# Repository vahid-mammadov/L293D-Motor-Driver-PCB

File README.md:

# L293D Motor Driver PCB

## Overview
A custom motor driver PCB designed for controlling DC motors using the **L293D H-Bridge motor driver**. 
The board was designed as part of an embedded systems and electronics development project.

## Features
Dual DC motor control using L293D
H-Bridge motor driver configuration
74HC595 shift register for digital output expansion
External power and motor connection interfaces
Custom schematic and PCB layout

## Tools & Technologies
**KiCad**
PCB Design
Electronic Circuit Design
L293D H-Bridge Motor Driver
74HC595 Shift Register

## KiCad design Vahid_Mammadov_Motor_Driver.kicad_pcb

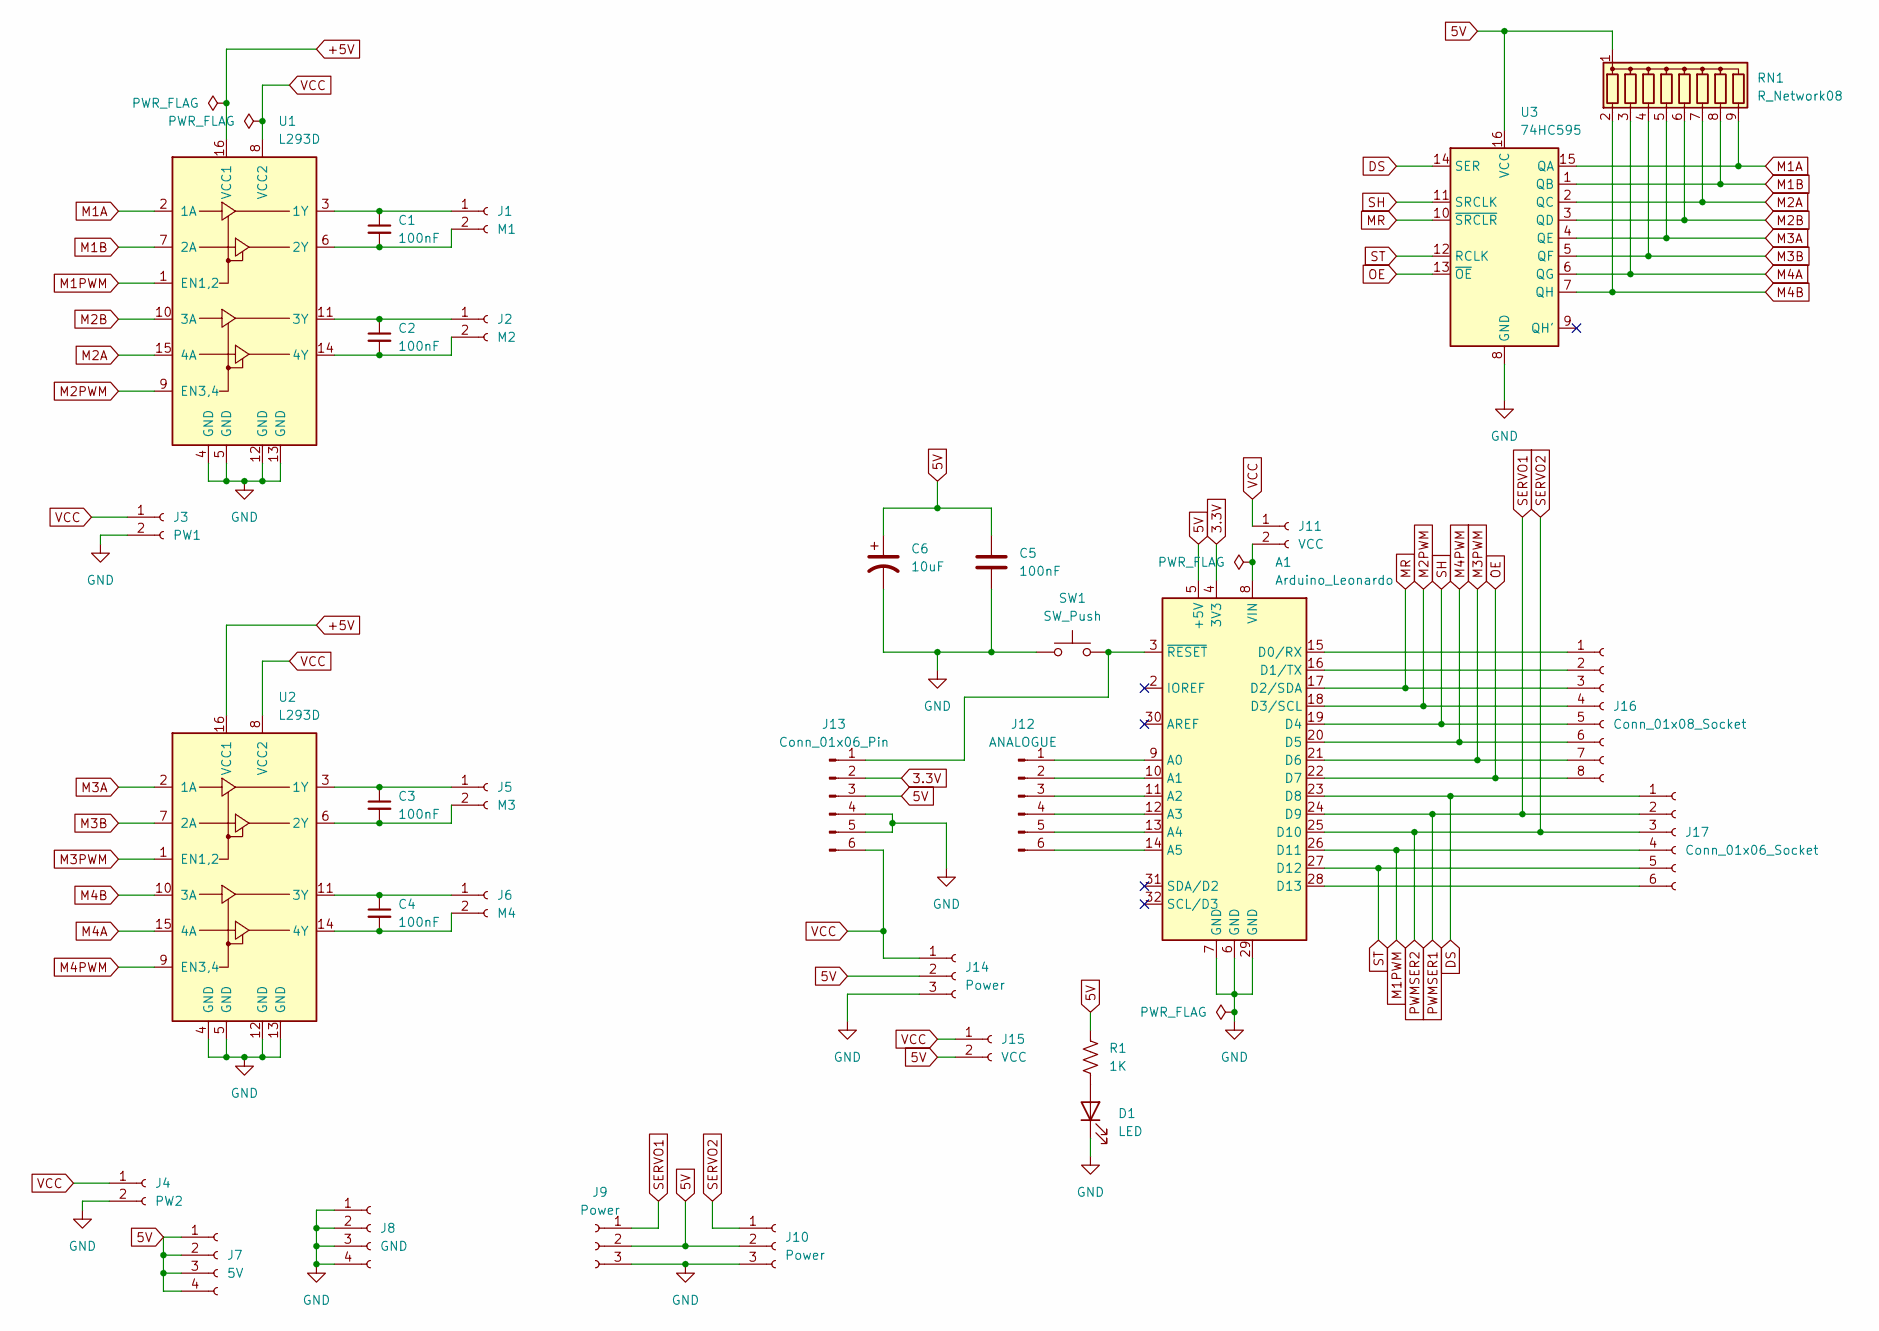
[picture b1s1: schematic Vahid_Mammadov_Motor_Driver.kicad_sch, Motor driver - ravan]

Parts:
A1: Arduino_Leonardo; Arduino_UNO_R3
C1, C2, C3, C4, C5: 100nF; CP_Radial_D4.0mm_P1.50mm
C6: 10uF; CP_Radial_D5.0mm_P2.50mm
D1: LED; LED_2010_5025Metric_Pad1.52x2.65mm_HandSolder
J1: M1; PinHeader_1x02_P2.00mm_Vertical
J2: M2; PinHeader_1x02_P2.00mm_Vertical
J3: PW1; PinHeader_1x02_P2.00mm_Vertical
J4: PW2; PinHeader_1x02_P2.00mm_Vertical
J5: M3; PinHeader_1x02_P2.00mm_Vertical
J6: M4; PinHeader_1x02_P2.00mm_Vertical
J7: 5V; PinHeader_1x04_P2.00mm_Vertical
J8: GND; PinHeader_1x04_P2.00mm_Vertical
J9, J10, J14: Power; PinHeader_1x03_P2.00mm_Vertical
J11, J15: VCC; PinHeader_1x02_P2.00mm_Vertical
J12: ANALOGUE; PinHeader_1x06_P2.00mm_Vertical
J13: Conn_01x06_Pin; PinHeader_1x06_P2.00mm_Vertical
J16: Conn_01x08_Socket; PinHeader_1x08_P2.00mm_Vertical
J17: Conn_01x06_Socket; PinHeader_1x08_P2.00mm_Vertical
R1: 1K; R_Axial_DIN0204_L3.6mm_D1.6mm_P5.08mm_Horizontal
RN1: R_Network08; R_Array_SIP9
SW1: SW_Push; SW_PUSH_6mm
U1, U2: L293D; DIP-16_W7.62mm
U3: 74HC595; DIP-16_W7.62mm

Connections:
3.3V: A1.4 (3V3), J13.2
5V: A1.5 (+5V), C5.1, C6.1, J7.1, J7.2, J7.3, J7.4, J9.2, J10.2, J13.3, J14.2, J15.2, R1.1, RN1.1 (common), U3.16 (VCC)
+5V: U1.16 (VCC1), U2.16 (VCC1)
DS: A1.23 (D8), J17.1, U3.14 (SER)
GND: A1.6 (GND), A1.7 (GND), A1.29 (GND), C5.2, C6.2, D1.1 (K), J3.2, J4.2, J8.1, J8.2, J8.3, J8.4, J9.3, J10.3, J13.4, J13.5, J14.3, SW1.1, U1.4 (GND), U1.5 (GND), U1.12 (GND), U1.13 (GND), U2.4 (GND), U2.5 (GND), U2.12 (GND), U2.13 (GND), U3.8 (GND)
M1A: RN1.9 (R8), U1.2 (1A), U3.15 (QA)
M1B: RN1.8 (R7), U1.7 (2A), U3.1 (QB)
M1PWM: A1.26 (D11), J17.4, U1.1 (EN1,2)
M2A: RN1.7 (R6), U1.15 (4A), U3.2 (QC)
M2B: RN1.6 (R5), U1.10 (3A), U3.3 (QD)
M2PWM: A1.18 (D3/SCL), J16.4, U1.9 (EN3,4)
M3A: RN1.5 (R4), U2.2 (1A), U3.4 (QE)
M3B: RN1.4 (R3), U2.7 (2A), U3.5 (QF)
M3PWM: A1.21 (D6), J16.7, U2.1 (EN1,2)
M4A: RN1.3 (R2), U2.15 (4A), U3.6 (QG)
M4B: RN1.2 (R1), U2.10 (3A), U3.7 (QH)
M4PWM: A1.20 (D5), J16.6, U2.9 (EN3,4)
MR: A1.17 (D2/SDA), J16.3, U3.10 (~SRCLR)
unnamed: A1.9 (A0), J12.1
unnamed: A1.10 (A1), J12.2
unnamed: A1.11 (A2), J12.3
unnamed: A1.12 (A3), J12.4
unnamed: A1.13 (A4), J12.5
unnamed: A1.14 (A5), J12.6
unnamed: A1.15 (D0/RX), J16.1
unnamed: A1.16 (D1/TX), J16.2
unnamed: A1.28 (D13), J17.6
unnamed: A1.8 (VIN), J11.2
unnamed: A1.3 (~RESET), J13.1, SW1.2
unnamed: D1.2 (A), R1.2
unnamed: C1.1, J1.1, U1.3 (1Y)
unnamed: C1.2, J1.2, U1.6 (2Y)
unnamed: C2.1, J2.1, U1.11 (3Y)
unnamed: C2.2, J2.2, U1.14 (4Y)
unnamed: C3.1, J5.1, U2.3 (1Y)
unnamed: C3.2, J5.2, U2.6 (2Y)
unnamed: C4.1, J6.1, U2.11 (3Y)
unnamed: C4.2, J6.2, U2.14 (4Y)
OE: A1.22 (D7), J16.8, U3.13 (~OE)
PWMSER1: A1.24 (D9), J9.1, J17.2
PWMSER2: A1.25 (D10), J10.1, J17.3
SH: A1.19 (D4), J16.5, U3.11 (SRCLK)
ST: A1.27 (D12), J17.5, U3.12 (RCLK)
VCC: J3.1, J4.1, J11.1, J13.6, J14.1, J15.1, U1.8 (VCC2), U2.8 (VCC2)

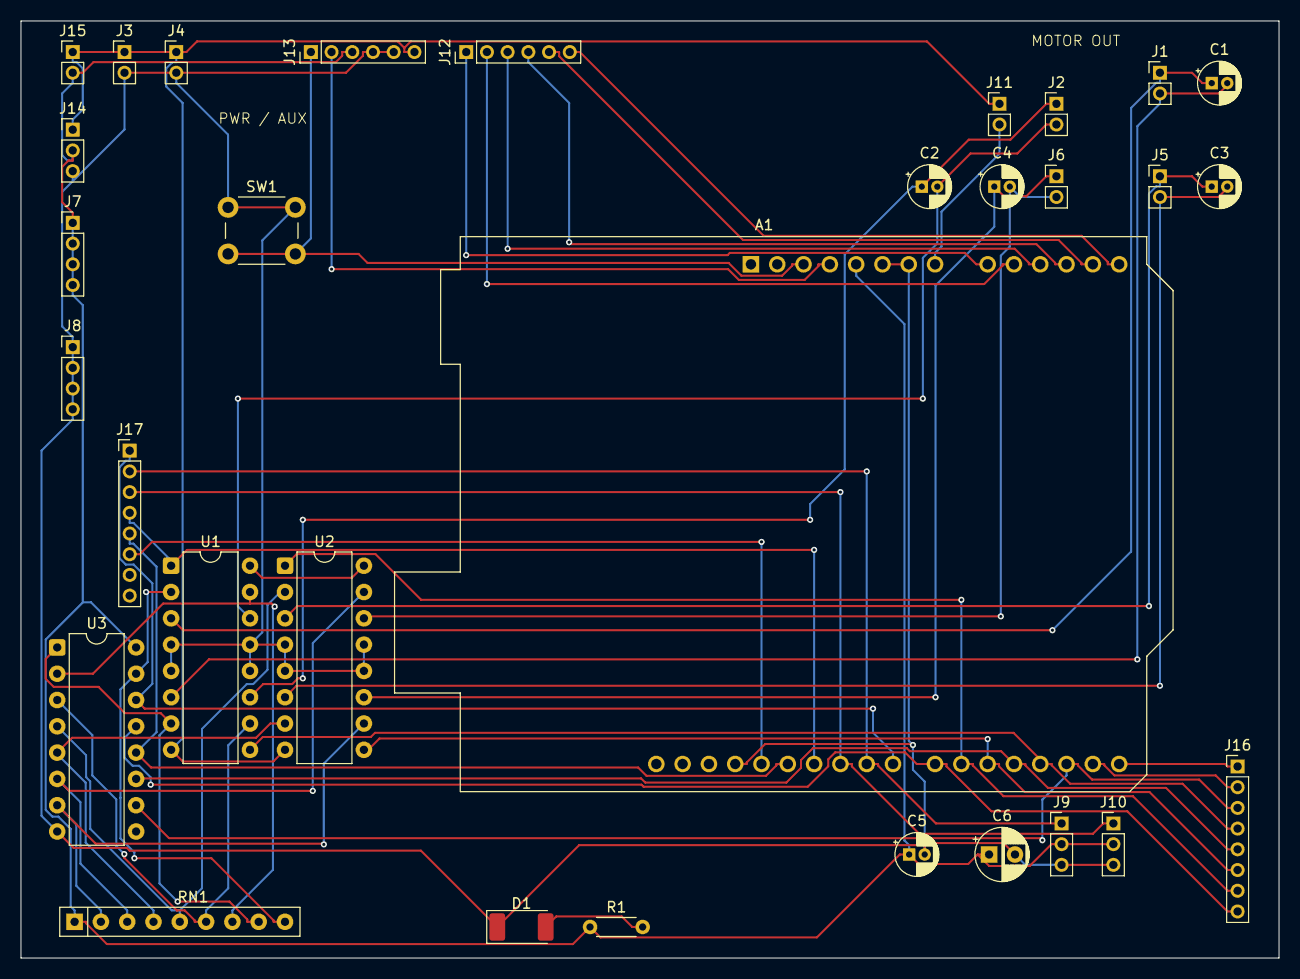
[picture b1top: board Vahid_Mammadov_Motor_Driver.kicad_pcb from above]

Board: 2 copper layers, 121.5 x 90.5 mm, 31 parts (0 on the bottom side), 44 nets.
